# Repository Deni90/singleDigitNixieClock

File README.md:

# Single Digit Nixie Clock

A small project combining ESP32 with a vintage Soviet Nixie tube from the 70’ to create an artistic clock.
Originally developed on ESP8266/Arduino, now evolved to ESP32 with ESP-IDF for greater performance and stability.

Huge thank you to **[PCBWay](https://www.pcbway.com)** for sponsoring this project!

For more details follow project logs on: **[my personal blog](https://deni90.github.io/projects/singledigitnixieclock/)** or **[hackaday.io](https://hackaday.io/project/202115-single-digit-nixie-clock)**

Some of the key features:
- Shows current time (hours and minutes) on a single nixie tube.
- Configurable RGB LED backlight lights up the nixie tube every second.
- USB powered.
- Hosts a web server for easy setup & configuration.
- Synchronises time with NTP server.

Operating modes:
- AP mode
  - This mode is hosting a dedicated open wifi network called `NixieClock`. Its main purpose is to use it for first time setup to update wifi configuration. In addition, this mode will be activated when the clock is not able to connect to a configured network. Clock hosts a captive portal. A configuration page will be opened automatically upon connecting to `NixieClock` network.
- Client mode
  - In this mode the clock is connected to a configured wifi network. If there is internet access, the clock will synchronize its RTC with NTP server at startup and then every hour periodically.

In both modes, the configuration page is easily reachable on the following URL: `<HOSTNAME>.local`. There is no need to keep track of the IP address, the clock is hosting Multicast DNS (mDNS) server. mDNS is supported by Chrome and Safari browsers out of the box.

By default, the `HOSTNAME` is set to `mynixieclock`.

## Firmware

This project started on ESP8266 with the Arduino framework, which was great for fast prototyping. However, the reliance on third-party libraries often led to instability and crashes.

To ensure long-term support and stability, the project was migrated from the now-obsolete ESP8266 to the ESP32, using ESP-IDF in C++.

This move provides:
- A robust and stable firmware base.
- Full access to ESP32’s hardware features.
- Use of official ESP-IDF components

### REST API

| End point | Method | Body (JSON) | Description |
| - | - | - | - |
| /api/v1/led/led_info | GET | {<br>&nbsp;&nbsp;&nbsp;&nbsp;“R”: <0-255>,<br>&nbsp;&nbsp;&nbsp;&nbsp;“G”: <0-255>,<br>&nbsp;&nbsp;&nbsp;&nbsp;“B”: <0-255>,<br>&nbsp;&nbsp;&nbsp;&nbsp;“state”: <0-2><br>} | Get color and state of the backlight (RGB LED). |
| /api/v1/led/led_info | POST | {<br>&nbsp;&nbsp;&nbsp;&nbsp;“R”: <0-255>,<br>&nbsp;&nbsp;&nbsp;&nbsp;“G”: <0-255>,<br>&nbsp;&nbsp;&nbsp;&nbsp;“B”: <0-255>,<br>&nbsp;&nbsp;&nbsp;&nbsp;“state”: <0-2><br>} | Set color and state of the backlight (RGB LED). |
| /api/v1/clock/sleep_info | GET | {<br>&nbsp;&nbsp;&nbsp;&nbsp; “sleep_before”: \<value>,<br>&nbsp;&nbsp;&nbsp;&nbsp; “sleep_after”: \<value><br>} | Get sleep mode configuration. The time before and after (in minutes) the backlight will be turned off. |
| /api/v1/clock/sleep_info | POST | {<br>&nbsp;&nbsp;&nbsp;&nbsp; “sleep_before”: \<value>,<br>&nbsp;&nbsp;&nbsp;&nbsp; “sleep_after”: \<value><br>} | Set sleep mode configuration. |
| /api/v1/clock/time_info | GET | {<br>&nbsp;&nbsp;&nbsp;&nbsp;"tz_zone": "\<Geographic zone>",<br>&nbsp;&nbsp;&nbsp;&nbsp;“tz_offset”: “\<Proleptic TZ>",<br>&nbsp;&nbsp;&nbsp;&nbsp;"time_format": \<"12h" \| "24h"><br>} | Get time zone configuration |
| /api/v1/clock/time_info | POST | {<br>&nbsp;&nbsp;&nbsp;&nbsp;"tz_zone": "\<Geographic zone>",<br>&nbsp;&nbsp;&nbsp;&nbsp;“tz_offset”: “\<Proleptic TZ>",<br>&nbsp;&nbsp;&nbsp;&nbsp;"time_format": \<"12h" \| "24h"><br>} | Set time zone configuration |
| /api/v1/wifi/wifi_info | GET | {<br>&nbsp;&nbsp;&nbsp;&nbsp;"hostname": "\<HOSTNAME>",<br>&nbsp;&nbsp;&nbsp;&nbsp;“SSID”: “\<Wifi SSID>”,<br>&nbsp;&nbsp;&nbsp;&nbsp;"auth_type": \<"open" \| "wpa2" \| "wpa3">,<br>&nbsp;&nbsp;&nbsp;&nbsp;“password”: “\<base64 encoded password>”<br>} | Get wifi configuration. |
| /api/v1/wifi/wifi_info | POST | {<br>&nbsp;&nbsp;&nbsp;&nbsp;"hostname": "\<HOSTNAME>",<br>&nbsp;&nbsp;&nbsp;&nbsp;“SSID”: “\<Wifi SSID>”,<br>&nbsp;&nbsp;&nbsp;&nbsp;"auth_type": \<"open" \| "wpa2" \| "wpa3">,<br>&nbsp;&nbsp;&nbsp;&nbsp;“password”: “\<base64 encoded password>”<br>} | Set wifi configuration. | Set wifi configuration. |

### Front-end layout & design

Initially, the front end was implemented with jQuery mobile. Reason for choosing this framework was in its simplicity. It provides a simple way to create and control user interface components. One thing that always annoyed me was its low response time. It took too much time to load jQuery, jQueryMobile and theme resources. On top of this, this slow response time caused WDT resets.

One more thing, I just realised that  jQuery mobile project is deprecated since October 7, 2021. Huh, when it comes to web related technologies, it looks like I'm living under a rock...

To solve these issues, I opted to completely re implement the frontend using plain HTML, CSS and JavaScript. The end result looks almost the same as the previous design or even better. Responsiveness and stability increased significantly. The only drawback is now in maintenance and extension. It is required to implement everything manually.

## Design

Schematic and PCB are designed with KiCAD

### Control board

Control board is basically a re-packaged generic ESP32 board design connected with DS3231 real time clock and NCH8200HV high voltage boost module board.

#### Schematic

### Display board

Display board uses a CD4028 BCD-to-decimal decoder. Its purpose is to reduce the number of required GPIO pins from 10 to just 4 for showing digits from 0 to 9. Compared to dedicated BCD to decimal decoder nixie drivers (like K511ID1), the CD4028 is a widely spread component and it is available in SMD package. Since CD4028 has a voltage range from 3.0V to 15V it is not compatible with nixie tube’s operating voltage of 170V out of the box. This problem is solved with MMBTA42, a high voltage transistor, rated to more than 200V.

The rest of the display board consists of a WS2812B RGB LED and a pin header used to connect with the control board.

#### Schematic

## PCB manufacturing

A representative from **PCBWay** contacted me because he was deeply impressed by my project and offered to sponsor a batch of PCBs to test out their services.

Since I recently moved to KiCad, it was a perfect opportunity to try out the PCBWay Plug-in for KiCad. It provides a simple way to place an order in just a few clicks. There is no need to bother with exporting gerber files, everything is automated. You just need to update the PCB specification and fill in the shipping information on the webpage. That’s it.

The entire journey from placing the order to receiving the package took less than a week. Incredible! PCBWay did a superb job, PCBs are amazing. I am more than impressed.

## Enclosure design

3D model is made with Autodesk Fusion 360.

The end result is a simple box shaped design with holes for the nixie tube and USB connector.

## Third-party dependencies

This project includes `firmware/flash_data/frontend/zones.json` from https://github.com/nayarsystems/posix_tz_db, licensed under the MIT License.

## Resources

* [IN-14 Nixie tube datasheet](https://tubehobby.com/datasheets/in14.pdf)
* [NCH8200HV High Voltage DC-DC Booster module](http://omnixie.io/nch8200hv.html)
* [CD4028 datasheet](https://www.renesas.com/en/document/dst/cd4028bms-datasheet?srsltid=AfmBOoqU2NILPd5EzyLmpNgOihDv6LZo1jPMcaXfnR6dCclXbg2DF4TL)

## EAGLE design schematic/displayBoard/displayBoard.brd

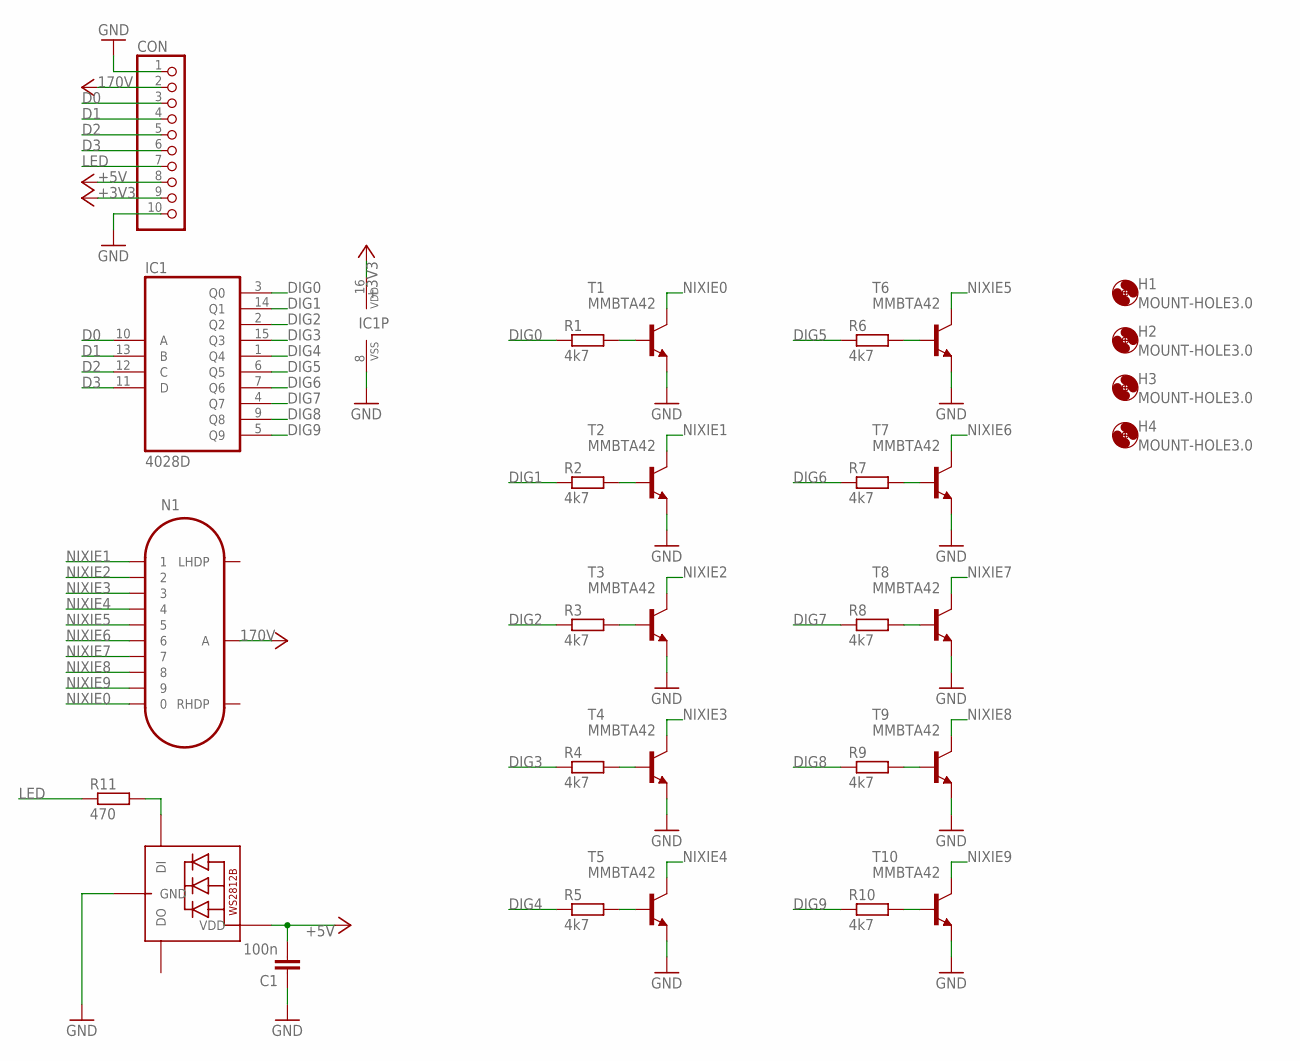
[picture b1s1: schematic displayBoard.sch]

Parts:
C1: 100n; C0603
CON: PINHD-1X10; 1X10
H1, H2, H3, H4: MOUNT-HOLE3.0; 3,0
IC1: 4028D; SO16
LED1: WS2812B_5050N; WS2812B-NARROW
N1: IN-14
R1, R2, R3, R4, R5, R6, R7, R8, R9, R10: 4k7; R0603
R11: 470; R0603
T1, T2, T3, T4, T5, T6, T7, T8, T9, T10: MMBTA42; SOT23-BEC

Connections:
+3V3: CON.9, IC1.16 (VDD)
+5V: C1.2, CON.8, LED1.1-VDD (VDD)
D0: CON.3, IC1.10 (A)
D1: CON.4, IC1.13 (B)
D2: CON.5, IC1.12 (C)
D3: CON.6, IC1.11 (D)
DIG0: IC1.3 (Q0), R1.1
DIG1: IC1.14 (Q1), R2.1
DIG2: IC1.2 (Q2), R3.1
DIG3: IC1.15 (Q3), R4.1
DIG4: IC1.1 (Q4), R5.1
DIG5: IC1.6 (Q5), R6.1
DIG6: IC1.7 (Q6), R7.1
DIG7: IC1.4 (Q7), R8.1
DIG8: IC1.9 (Q8), R9.1
DIG9: IC1.5 (Q9), R10.1
GND: C1.1, CON.1, CON.10, IC1.8 (VSS), LED1.3-GND (GND), T1.E, T2.E, T3.E, T4.E, T5.E, T6.E, T7.E, T8.E, T9.E, T10.E
LED: CON.7, R11.1
unnamed: R1.2, T1.B
unnamed: R2.2, T2.B
unnamed: R3.2, T3.B
unnamed: R4.2, T4.B
unnamed: R5.2, T5.B
unnamed: R6.2, T6.B
unnamed: R7.2, T7.B
unnamed: R8.2, T8.B
unnamed: R9.2, T9.B
unnamed: R10.2, T10.B
unnamed: LED1.4-DIN (DI), R11.2
NIXIE0: N1.0, T1.C
NIXIE1: N1.1, T2.C
NIXIE2: N1.2, T3.C
NIXIE3: N1.3, T4.C
NIXIE4: N1.4, T5.C
NIXIE5: N1.5, T6.C
NIXIE6: N1.6, T7.C
NIXIE7: N1.7, T8.C
NIXIE8: N1.8, T9.C
NIXIE9: N1.9, T10.C
VCC: CON.2, N1.A

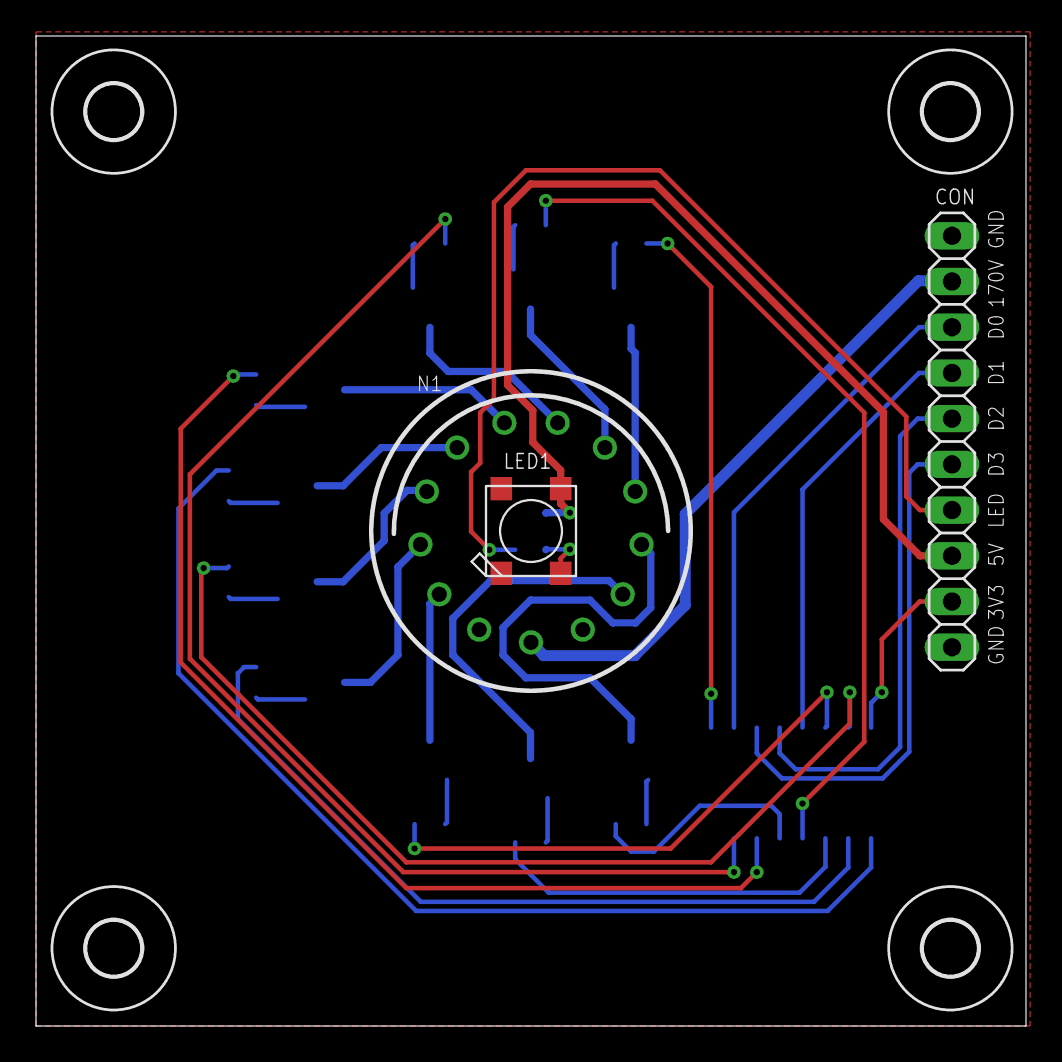
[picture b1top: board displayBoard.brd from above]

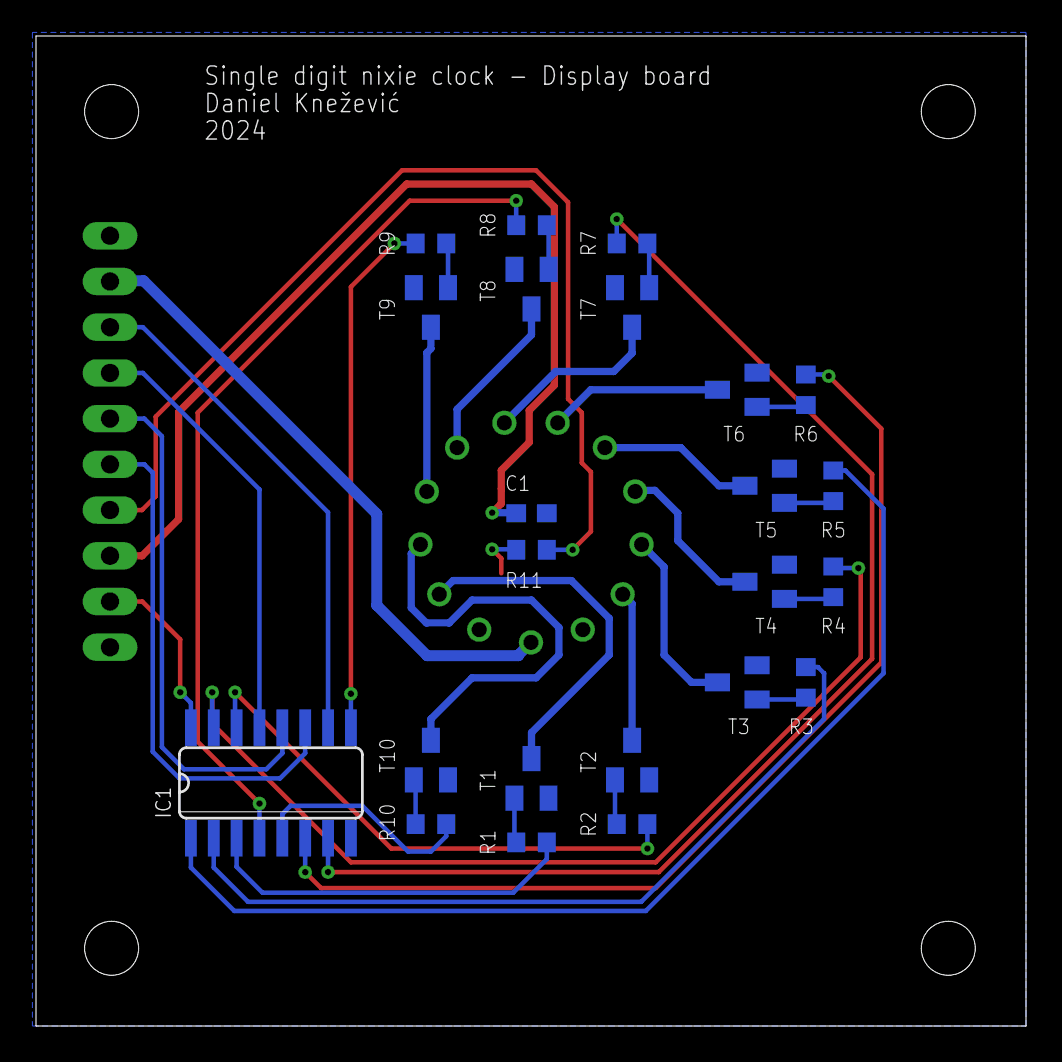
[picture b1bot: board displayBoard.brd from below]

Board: 2 copper layers, 55.0 x 55.0 mm, 30 parts (23 on the bottom side), 40 nets.

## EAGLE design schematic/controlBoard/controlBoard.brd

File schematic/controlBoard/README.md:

# Control board

**IMPORTANT**: After calling "Update PCB from Schematic..."(F8) it is needed to manually change the layout of Y1 to:

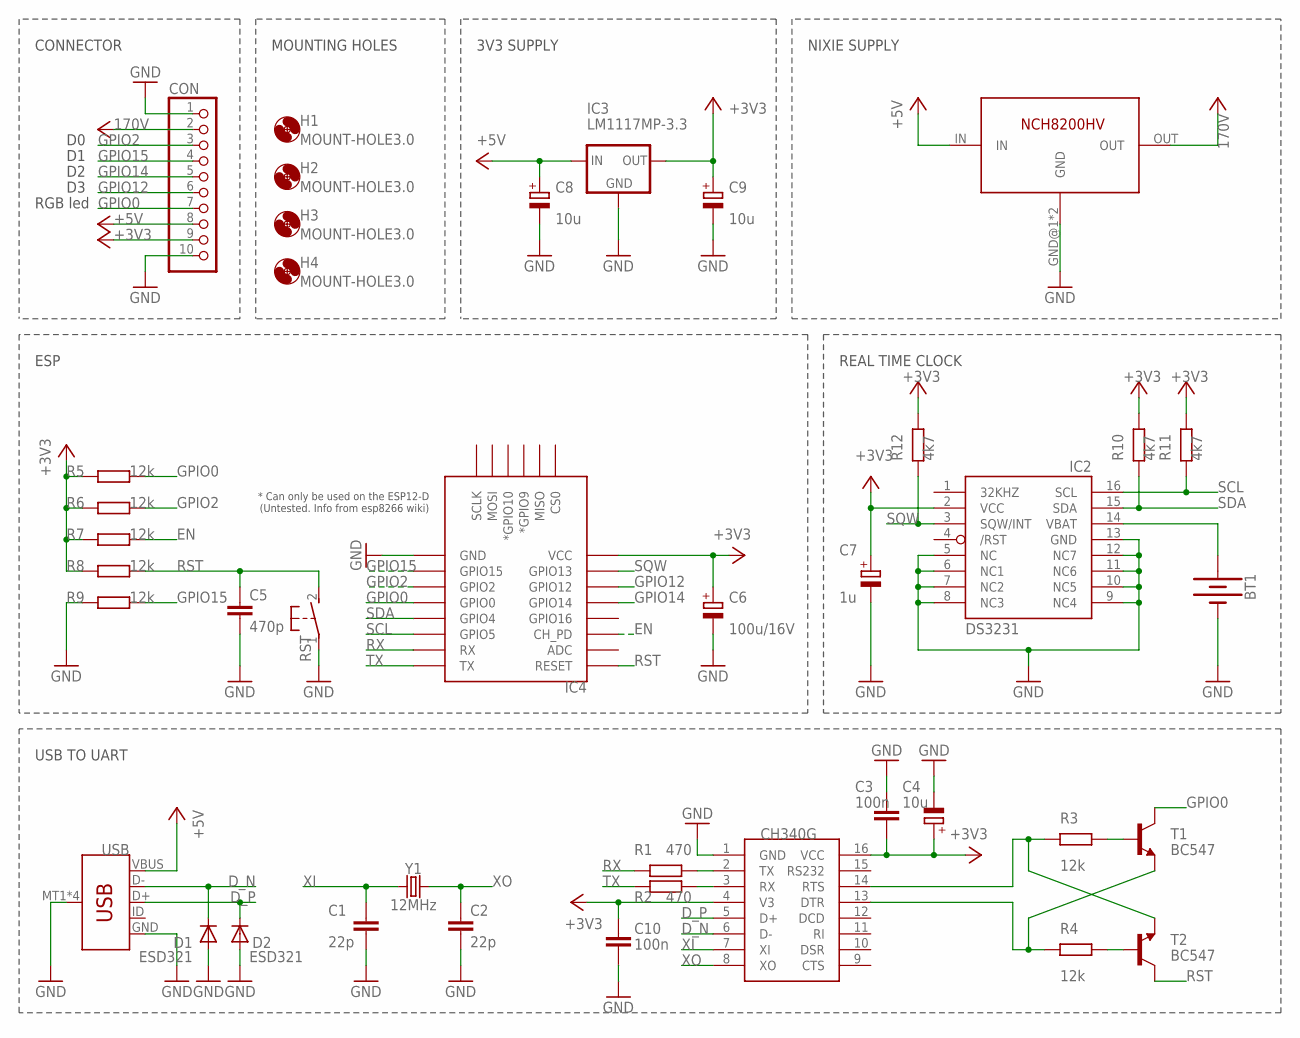
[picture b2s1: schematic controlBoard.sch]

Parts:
1: NCH8200HV
BT1: BATTERY-20MM_PTH; BATTCOM_20MM_PTH
C1, C2: 22p; C0603
C3, C10: 100n; C0603
C4, C8, C9: 10u; SMC_A
C5: 470p; C0603
C6: 100u/16V; SMC_D
C7: 1u; SMC_A
CON: PINHD-1X10; 1X10
D1, D2: ESD321; SOD523
H1, H2, H3, H4: MOUNT-HOLE3.0; 3,0
IC2: DS3231/SO; SO16W
IC3: LM1117MP-3.3; SOT223
IC4: ESP12ESMD; ESP12E-SMD
R1, R2: 470; R0603
R3, R4, R5, R6, R7, R8, R9: 12k; R0603
R10, R11, R12: 4k7; R0603
RST: 31-XX; B3F-31XX
T1, T2: BC547; SOT23-BEC
U$2: CH340G; SOIC16
USB: USB_MICRO-B_SMT; USB-MICROB
Y1: 12MHz; CRYSTAL-SMD-5X3.2-4PAD

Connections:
+3V3: C3.2, C4.+, C6.+, C7.+, C9.+, C10.1, CON.9, IC2.2 (VCC), IC3.2 (OUT), IC3.4 (OUT), IC4.VCC, R5.2, R6.2, R7.2, R8.2, R10.1, R11.1, R12.1, U$2.4 (V3), U$2.16 (VCC)
+5V: 1.IN, C8.+, CON.8, IC3.3 (IN), USB.VBUS
D_N: D1.C, U$2.6 (D-), USB.D-
D_P: D2.C, U$2.5 (D+), USB.D+
EN: IC4.CH_PD, R7.1
GND: 1.GND@1 (GND), 1.GND@2 (GND), BT1.2 (-), C1.1, C2.1, C3.1, C4.-, C5.2, C6.-, C7.-, C8.-, C9.-, C10.2, CON.1, CON.10, D1.A, D2.A, IC2.5 (NC), IC2.6 (NC1), IC2.7 (NC2), IC2.8 (NC3), IC2.9 (NC4), IC2.10 (NC5), IC2.11 (NC6), IC2.12 (NC7), IC2.13 (GND), IC3.1 (GND), IC4.GND, R9.2, RST.1, U$2.1 (GND), USB.GND, USB.MT1 (SHIELD), USB.MT2 (SHIELD), USB.P$1 (SHIELD), USB.P$2 (SHIELD)
GPIO0: CON.7, IC4.GPIO0, R5.1, T1.C
GPIO2: CON.3, IC4.GPIO2, R6.1
GPIO12: CON.6, IC4.GPIO12
GPIO14: CON.5, IC4.GPIO14
GPIO15: CON.4, IC4.GPIO15, R9.1
unnamed: R1.1, U$2.2 (TX)
unnamed: R2.1, U$2.3 (RX)
unnamed: R4.2, T1.E, U$2.13 (DTR)
unnamed: R3.1, T1.B
unnamed: R4.1, T2.B
unnamed: BT1.1 (+), IC2.14 (VBAT)
unnamed: R3.2, T2.E, U$2.14 (RTS)
RST: C5.1, IC4.RESET, R8.1, RST.2 (S), T2.C
RX: IC4.RXD0 (RX), R1.2
SCL: IC2.16 (SCL), IC4.GPIO5, R11.2
SDA: IC2.15 (SDA), IC4.GPIO4, R10.2
SQW: IC2.3 (SQW/INT), IC4.GPIO13, R12.2
TX: IC4.TXD0 (TX), R2.2
VCC: 1.OUT, CON.2
XI: C1.2, U$2.7 (XI), Y1.1
XO: C2.2, U$2.8 (XO), Y1.3 (2)

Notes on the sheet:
USB TO UART
REAL TIME CLOCK
RGB led
3V3 SUPPLY
ESP
CONNECTOR
MOUNTING HOLES
NIXIE SUPPLY

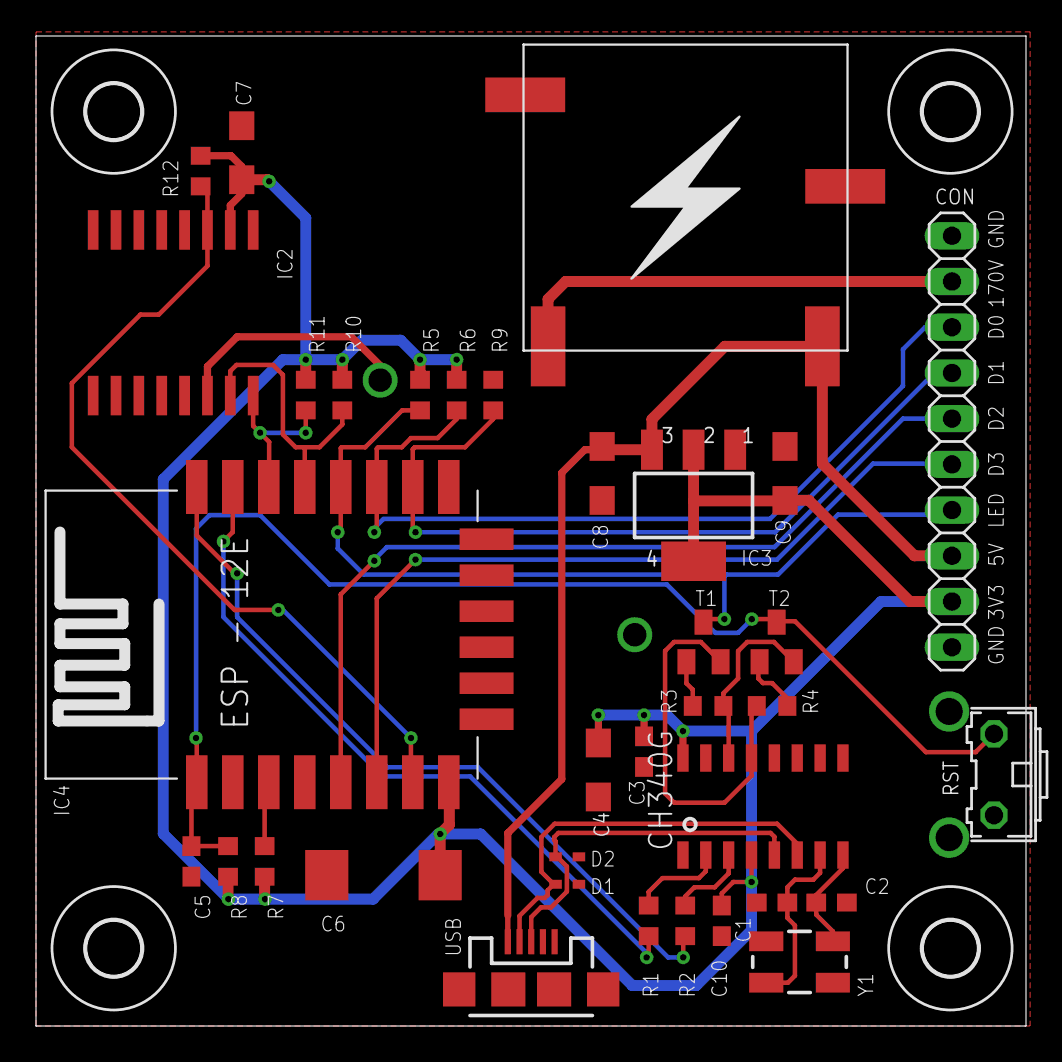
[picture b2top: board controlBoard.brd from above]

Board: 2 copper layers, 55.0 x 55.0 mm, 40 parts (1 on the bottom side), 27 nets.

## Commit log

2020-04-23 Updated README file
2020-05-06 Refactored usage of timers and enabled SQW of DS3231
    - changed led pin to D3
    - enabled interrupt for SQW
2020-05-06 Renamed UpdateState to Update in LedController.
2020-05-06 Implemented BCD 2 decimal decoder
2022-04-01 Added display board schematic & PCB design
2022-04-01 Moved displayBoard under schematic folder
2022-04-06 Removed white spaces from LedController
2022-04-06 Separated led info from led controller
    Led information like color and state are moved to a separate module.
2022-04-06 EEPROM hangling is moved under ConfigStore module
    Config store module is responsible for loading and saving device's
    configurations like led color, led status, ...
2022-04-06 Created ClockFace module to handle time animations.
    Main has been refactored by moving nixie & led handling into a
    sepatare module.
2022-04-06 Adafruit_NeoPixel is moved under LedController
2022-04-06 Defines converted to constexpr & added splash screen
2022-04-07 Updated LedState to have ON, OFF and FADE states
2022-04-11 Removed vscode folder
2022-04-11 Implemented a web server by using jquery mobile
    - REST server has been replaced by ESP8266WebServer
    - Web page is stored on flash by using LittleFS file system
    - Backlight control has been implemented with ClockInterface
2022-04-12 Implemented set color in web server
2022-04-12 Refactored LED handling
    - removed alpha from classes and interfaces
    - fading is simplified by modifying only the brightness
2023-12-27 Create an adapter to fix showing wrong digits
    Create In18NixieTube to adapt BCD2DecimalDecoder so that correct
    digits are shown on the nixie tube.
    For some reason the pinout of the IN-18 tube does not match with
    Eagle's component.
2023-12-27 Fine tune animation timeouts and reverse intro
2023-12-28 Reformat code
2023-12-28 Move source to firmware folder
2023-12-28 Add backlight configuration to server
    - enable setting backlight brightness, mode and color
2023-12-28 Add set current time to REST API
2023-12-28 Add clang-format & reformat code
2023-12-29 Refactor WebServer
    - Replace ESP8266WebServer with AsyncWebServer
    - Simplify module by removing singleton
2023-12-29 Add an option for pulsing LED
2023-12-29 Remove AlwaysBreakAfterReturnType from clang-format
2023-12-29 Make truthTable const
2023-12-29 Remove formatSwitch from HTML page
2023-12-29 Show time after it is updated via REST API
    - Refactor ClockFace to accept the number of repeats whren showing time
2023-12-30 Rename In18NixieTube module to In14NixieTube
2024-01-03 Reduce the size of the controll board
2024-01-03 Add README & images to CB
2024-01-03 Add control board schematic
2024-02-01 Supply CH340 with 3V3 to fix ESP programming issue
    In order to properly communicate with ESP it is required to use CH340
    USB to serial in 3V3 mode.
2024-02-02 Add ESD protection to USB data lanes
2024-02-02 Add title to PCBs
2024-02-02 Update schematic images
2024-10-07 Add doxygen comments
2024-10-07 Remove ci variable
2024-10-07 Refactor In14NixieTube by encapsulating BCD2DecimalDecoder
2024-10-07 Change SSID
2024-10-10 Simplify WebServer by combining paths
    - Combine backlight related paths into Get/Set methods.
    - Add lock to led controller to prevent updating led state while showing
    time.
    - Update index.html to use the new REST API.
2024-10-10 Rename counter to secondsCounter and fix buffer size
2024-10-16 Refactor HandleGetLedInfo
    - Use JsonDocument instead of StaticJsonDocument
    - Use String instead of char buffer
    - Use serializeJson instead of serializeJsonPretty to shorten the JSON
    message
2024-10-16 Move ShowTime to HandleInterrupt interrupt routine
2024-10-28 Rename label to Color preview
2024-10-31 Move implementation of ClockInterface to NixieClock
    - Move implementation of ClockInterface to ClockFace
    - Remove NixieClockInterface class
    - Rename ClockFace class to NixieClock
2024-11-01 Add headings to tabs
2024-11-01 Fix OnGetLedInfo to get info from ConfigStore
2024-11-01 Update time format in prints
2024-11-01 Check for NULL in WebServer::Handle functions
2024-11-01 Rename backlight to ledInfo
2024-11-02 Implement sleep mode feature
    Sleep mode turns off the led and nixie tube for a configured time period
2024-11-02 Rename Load/StoreLedConfiguration to Load/StoreLedInfo
2024-11-02 Fix updating led info while in sleep mode
2024-11-05 Add readme file to the project
2024-11-17 Replace image with gif
2024-11-18 Update readme files
2024-12-28 Update dependencies
2024-12-28 Refactor ConfigStore to use LittleFS
    - Replace EEPROM with json config files
2024-12-28 Add ToJson() to LedInfo and SleepInfo classes
    - Update ConfigStore and WebServer to use ToJson().
2024-12-28 Make prints in setup() pretty
2024-12-28 Load Wifi SSID and password from a JSON file
2024-12-28 Move web server files to a dedicated folder
2024-12-28 Add wifi tab to web page
    - Extend ConfigStore with SaveWifiInfo function.
    - Extend WebServer with /wifi GET and POST methods.
    - Update web page with a wifi tab.
2024-12-28 Fix colorBox init and currentTime label access
2024-12-30 Update firmware's readme file
2025-01-01 Add more comments to NixieClock::Handle
2025-01-01 Convert EaglePCB projects to KiCad
2025-01-06 Connect clock to a local wifi network
    - By default configure clock to use wifi in station mode.
    - Try to connect to the configured wifi network
    - If it is not possible to connect to a configured network switch to AP mode
    - Use different DnsServer for captive portal in AP mode
    - Use MDNS for station mode
2025-01-06 Remove 'ap' prefix from wifi tab
2025-01-07 Synchronise time via NTP
    - Create TimeInfo for storing time related configuration
    - Create TimeManager for getting time from NTP server
2025-01-07 Make time zone configurable via web server
2025-01-07 Remove printing out config and remove default wifi credentials
2025-01-11 Re-implement web server to improve performance and stability
    - Remove dependency to jQuery mobile
    - Use plain javascript for the front-end implementation
    - Define a cutom css style to follow existing UI design
    - Refactor WebServer REST api handling to use AsyncCallbackJsonWebHandler
    - Enable mDNS in AP mode
2025-01-11 Use usb type C connector and re-wire control board with KiCad components
2025-01-11 Remove formatting from config files
2025-01-11 Refactor *DNS usage
2025-01-12 Enter sleep mode right after config is updated
2025-01-12 Modify SleepInfo to use minutes and update frontend
2025-01-12 Re-wire control display with KiCad components
2025-01-12 Update images of new PCBs
2025-01-12 Update main readme file
2025-01-13 Add front-end section to README
2025-01-14 Describe operating modes
2025-01-16 Update control board with updated usb-c wiring
2025-01-18 Make hostname configurable via web app
2025-01-22 Add model diagrams to Readme
2025-01-30 Fix weird behaviour of the LED by adding a level shifter to DIN pin
2025-01-31 Match via sizes between two PCBs
2025-02-11 Update README with hackaday link and PCBWay sponsorship
2025-02-28 Add enclosure model to repo
2025-03-30 Replace agdl/Base64 with densaugeo/base64 library
2025-03-30 Replace PlatformIO with Makefile
    To simplify project setup, the Arduino core for ESP8266 and all dependencies are moved to be part of the project as git submodules. This way, there is no need to manualy download and setup Arduino ID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
2025-04-06 Make choice handling more generic
2025-04-06 Add support for daylight saving time
2025-04-09 Re-enable password sharing in HandleGetWifiInfo
2025-04-09 Setup AP mode when the wifi SSID is empty
2025-04-09 Log wifi SSID and hostname in setup()
2025-06-03 Update README with a finished product
2025-08-18 Remove C4 diagrams from README
2025-08-30 Use ESP32 instead of ESP8266
    - Re-route PCB to support ESP32
    - Fill top plane with +3v3
2025-08-30 Rename schematic folder to hardware
2025-08-31 Finalize PCB design
2025-09-06 Port firmware to ESP32
    - Replace Arduino with ESP-IDF
    - Remove third-party git submodules
    - Use built-in ESP-EDF components for Wifi, LED, mDNS, DNS, FS, HTTP server, ...
    - Simplify nixie clock's logic by using freeRTOS tasks
2025-09-06 Add LED animation to initialize function of LedController
    - test() function is iterating through RGB colors at startup
2025-09-06 Add REST API versioning
    - Refactor WebServer's REST API to include API version
    - Update front-end to use the new REST API
2025-09-06 Add pull-ups to BCD decoder inputs
    - Add pull-up resistors to BCD decoder to prevent turning on the nixie tube during boot
2025-09-06 Set tab button witdth based on number of tabs
2025-09-06 Fix typos in server.js
2025-09-06 Load data on when opening a tab
2025-09-06 Remove global variables from front-end code
2025-09-06 Use 'let' instead of 'var'
2025-09-06 Update README with control board schematic
2025-09-07 Add a decoupling cap to CD4028
2025-09-08 Check is sleep mode active during startup
2025-09-10 Refactor led controller's temporal led state handling
    - Remove "locking" mechanism and replace it with temporal state
2025-09-10 Fix comments
2025-09-10 Add support for showing 12 and 24 hour formats
2025-09-11 Move littlefs setup to ConfigStore class
2025-09-11 Move wifi handling to WifiManager module
2025-09-27 Reorganize doc
    - rename images
    - update README.md with new file names and alt text
2025-09-27 Cosmetic fix on control board schematic
2025-09-27 Update image for front-end design
2025-09-29 Add authentication type to Wifi
    Add authentication type to Wifi so that the user can choose between open, WPA2 or WPA3 types when configuring the connection to a Wifi network.
2025-09-29 Update README with REST API doc and new front-end conaining wifi changes
2025-10-03 Implement getting time from RTC if NTP is not available
    - Implement an I2C OOP wrapper around ESP-IDF's i2c_master
    - Implement get/set time for DS3231 RTC
    - Integrate RTC handling to NixieClock
2025-10-07 Fix auto-programming circuit issue
    - Add pullups to EN and IO0 pins.
    - Add 100nF ceramic capacitor between EN and GND to improve timimng.
2025-10-10 Add copper thief to the bottom layer of display board
2025-10-19 Update assembled PCB image
2025-11-02 Fix entering/exiting sleep mode
2025-11-12 Fix exiting sleep mode
    Always start loop task in initialize function, regardless of being in sleep mode.
2025-12-09 Make a RAII wrapper for a FreeRTOS mutex
    - The mutex wrapper is compatible with std::lock_guard.
    - Code has been updated to use the new mutex.
2025-12-18 Add missing partition table to project
2025-12-18 Add a bigger delay between animation intro and showing current time

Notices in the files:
parts and their libraries:
SparkFun-Connectors: Licensing: Creative Commons ShareAlike 4.0 International - https://creativecommons.org/licenses/by-sa/4.0
lm1117: (c) 2014 Samuel Lourenço
